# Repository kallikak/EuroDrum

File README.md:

# EuroDrum
Firmware source and schematics for the "Hit It!" Eurorack module.

<table>
  <tr>
    <td></td>
    <td></td>
    <td></td>
  </tr>  
</table>

This YouTube video gives a [brief overview](https://youtu.be/IKqNawbhtcc), and this one shows the [pitch CV mode](https://youtu.be/h47teE46W28).

The two encoders on the left let you move a cursor around the LED matrix, and the SET button toggles a connection between a beat (along the top) and a drum sample (down the side).

In "Bar" mode, the bar length is up to 8 beats, and the lit LEDs connect a beat to the instruments to be played on that beat.
In "Poly" mode, the lit LEDs mean play the corresponding instrument once every *n* beats.

Tone controls a LP filter, increasing cutoff until 12 o'clock, then decreasing while adding resonance. Decay is a simple decay envelope, and drive adds waveshaper distortion. Each control has an associated CV input below.

For timing, there is external gate in, as well as an internally generated clock (that is normalled to the gate in), and of course the audio out.

Hitting adjust switches between control modes:

- Normal mode as shown in the images where the encoders and SET button make and break connections.
  - A long press of SET toggles between active and inactive states.
  - A very long press of SET enters barlength mode, where continuing to hold SET while turning the left-right encoder will adjust the bar length for BAR mode.
  - A long press of ADJUST will clear all connections.
  - Continuing to hold ADJUST will restore a default set of connections.
- Levels mode for setting the level of each instrument. A long press of ADJUST will restore the default levels.
- Kit mode for selecting between 7 kits.
  - Each instrument has an alternate sample
  - The pairs are Bass/Clap, Snare/Rimshot, Open-hat/Maracas, Closed-hat/Claves, Crash cymbal/Ride cymbal, Toms/Congas.
  - Access is by selecting one of 7 pre-defined combinations. This way the front markings keep a reasonable meaning when changing the allocation.
  - Cycle kits with the SET button when in this mode (the display will show a letter from A to G).
- Sequencer mode where the outputs are pitch CVs.
  - The CV offset range from -0.41V to +1V corresponding to 8 offsets from down a 4th to up an octave, following a pentatonic major or minor scale. 
  - The SET button switches between scales (a + on the display indicates major and - indicates minor).
  - A long press of adjust will enable and disable the sequencer mode.

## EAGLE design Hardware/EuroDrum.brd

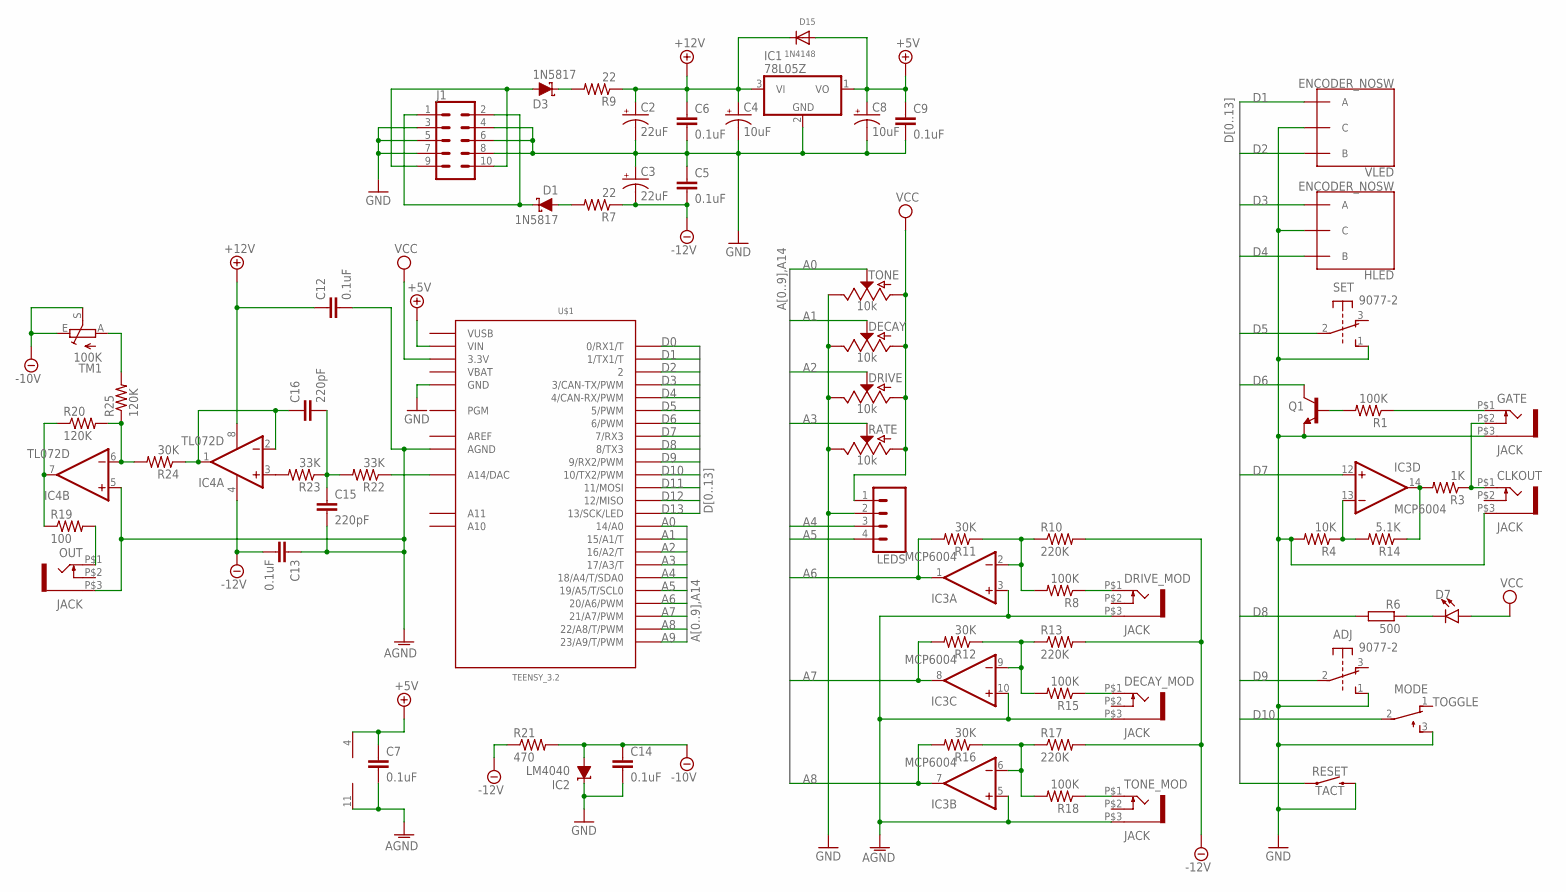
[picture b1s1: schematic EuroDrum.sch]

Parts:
ADJ: 9077-2
C2, C3: 22uF; CPOL-RADIAL-2.5MM-5MM
C4, C8: 10uF; CPOL-RADIAL-2.5MM-5MM
C5, C6, C7, C9, C12, C13, C14: 0.1uF; C0603K
C15, C16: 220pF; C0603K
CLKOUT: JACK; WQP-PJ301M-12_JACK
D1, D3: 1N5817; SOD-323
D7: LED3MM; LED_3MM
D15: 1N4148; SOD-123
DECAY: 10k; POT-PTH-ALPS
DECAY_MOD: JACK; WQP-PJ301M-12_JACK
DRIVE: 10k; POT-PTH-ALPS
DRIVE_MOD: JACK; WQP-PJ301M-12_JACK
GATE: JACK; WQP-PJ301M-12_JACK
HLED: ENCODER_NOSW
IC1: 78L05Z; TO92
IC2: LM4040; DBZ_R-PDSO-G3
IC3: MCP6004; SO14
IC4: TL072D; SO08
J1: CONN_05X2SHD; 2X5-SHROUDED
LEDS: CONN_04LONGPADS; 1X04_LONGPADS
MODE: TOGGLE; TL3XYO
OUT: JACK; WQP-PJ301M-12_JACK
Q1: BC549C; TO92-EBC
R1, R8, R15, R18: 100K; R0603
R3: 1K; R0603
R4: 10K; R0603
R6: 500; R0603
R7, R9: 22; R0603
R10, R13, R17: 220K; R0603
R11, R12, R16, R24: 30K; R0603
R14: 5.1K; R0603
R19: 100; R0603
R20, R25: 120K; R0603
R21: 470; R0603
R22, R23: 33K; R0603
RATE: 10k; POT-PTH-ALPS
RESET: TACT; TACTILE_SWITCH_PTH_6.0MM
SET: 9077-2
TM1: 100K; CA6H
TONE: 10k; POT-PTH-ALPS
TONE_MOD: JACK; WQP-PJ301M-12_JACK
U$1: TEENSY_3.2; TEENSY_3.0-3.2&LC_ALL_PINS
VLED: ENCODER_NOSW

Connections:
+5V: C7.1, C8.1 (+), C9.1, D15.A, IC1.1 (VO), IC3.4 (V+), U$1.VIN
+12V: C2.1 (+), C4.1 (+), C6.1, C12.1, D15.C, IC1.3 (VI), IC4.8 (V+), R9.1
-10V: C14.1, IC2.2 (A), R21.2, TM1.E, TM1.S
-12V: C3.2 (-), C5.2, C13.2, IC4.4 (V-), R7.1, R10.2, R13.2, R17.2, R21.1
A0: TONE.P$2 (S), U$1.14/A0
A1: DECAY.P$2 (S), U$1.15/A1 (15/A1/T)
A2: DRIVE.P$2 (S), U$1.16/A2 (16/A2/T)
A3: RATE.P$2 (S), U$1.17/A3 (17/A3/T)
A4: LEDS.3, U$1.18/A4 (18/A4/T/SDA0)
A5: LEDS.4, U$1.19/A5 (19/A5/T/SCL0)
A6: IC3.1 (OUT), R11.2, U$1.20/A6 (20/A6/PWM)
A7: IC3.8 (OUT), R12.2, U$1.21/A7 (21/A7/PWM)
A8: IC3.7 (OUT), R16.2, U$1.22/A8 (22/A8/T/PWM)
A9: U$1.23/A9 (23/A9/T/PWM)
AGND: C7.2, C12.2, C13.1, C15.2, DECAY_MOD.P$3 (1), DRIVE_MOD.P$3 (1), IC3.3 (+IN), IC3.5 (+IN), IC3.10 (+IN), IC3.11 (V-), IC4.5 (+IN), OUT.P$3 (1), TONE_MOD.P$3 (1), U$1.AGND
AREF: U$1.AREF
D0: U$1.0 (0/RX1/T)
D1: U$1.1 (1/TX1/T), VLED.A
D2: U$1.2, VLED.B
D3: HLED.A, U$1.3 (3/CAN-TX/PWM)
D4: HLED.B, U$1.4 (4/CAN-RX/PWM)
D5: SET.2, U$1.5 (5/PWM)
D6: Q1.C, U$1.6 (6/PWM)
D7: IC3.12 (+IN), U$1.7 (7/RX3)
D8: R6.2, U$1.8 (8/TX3)
D9: ADJ.2, U$1.9 (9/RX2/PWM)
D10: MODE.2, U$1.10 (10/TX2/PWM)
D11: RESET.1, U$1.11 (11/MOSI)
D12: U$1.12 (12/MISO)
D13: U$1.13 (13/SCK/LED)
GND: ADJ.1 (S), C2.2 (-), C3.1 (+), C4.2 (-), C5.1, C6.2, C8.2 (-), C9.2, C14.2, CLKOUT.P$3 (1), DECAY.P$1 (E), DRIVE.P$1 (E), GATE.P$3 (1), HLED.C, IC1.2 (GND), IC2.1 (C), J1.3, J1.4, J1.5, J1.6, J1.7, J1.8, LEDS.2, MODE.3 (S), Q1.E, R4.2, RATE.P$1 (E), RESET.3 (2), SET.1 (S), TONE.P$1 (E), U$1.GND, U$1.GND1 (GND), VLED.C
unnamed: D1.C, J1.1, J1.2
unnamed: IC3.9 (-IN), R12.1, R13.1, R15.2
unnamed: D3.A, J1.9, J1.10
unnamed: D3.C, R9.2
unnamed: DRIVE_MOD.P$1 (2), R8.1
unnamed: D1.A, R7.2
unnamed: IC3.2 (-IN), R8.2, R10.1, R11.1
unnamed: CLKOUT.P$1 (2), GATE.P$2 (3), R3.1
unnamed: DECAY_MOD.P$1 (2), R15.1
unnamed: IC3.6 (-IN), R16.1, R17.1, R18.2
unnamed: R18.1, TONE_MOD.P$1 (2)
unnamed: IC4.3 (+IN), R23.2
unnamed: Q1.B, R1.2
unnamed: C15.1, C16.2, R22.2, R23.1
unnamed: R22.1, U$1.RESET/DAC (A14/DAC)
unnamed: C16.1, IC4.1 (OUT), IC4.2 (-IN), R24.1
unnamed: GATE.P$1 (2), R1.1
unnamed: IC3.13 (-IN), R4.1, R14.2
unnamed: D7.K (C), R6.1
unnamed: IC4.6 (-IN), R20.2, R24.2, R25.1
unnamed: OUT.P$1 (2), R19.2
unnamed: IC4.7 (OUT), R19.1, R20.1
unnamed: R25.2, TM1.A
NOTE1: IC3.14 (OUT), R3.2, R14.1
VBAT: U$1.VBAT
VCC: D7.A, DECAY.P$3 (A), DRIVE.P$3 (A), LEDS.1, RATE.P$3 (A), TONE.P$3 (A), U$1.3.3V, U$1.3.3V1 (3.3V)
VUSB: U$1.VUSB

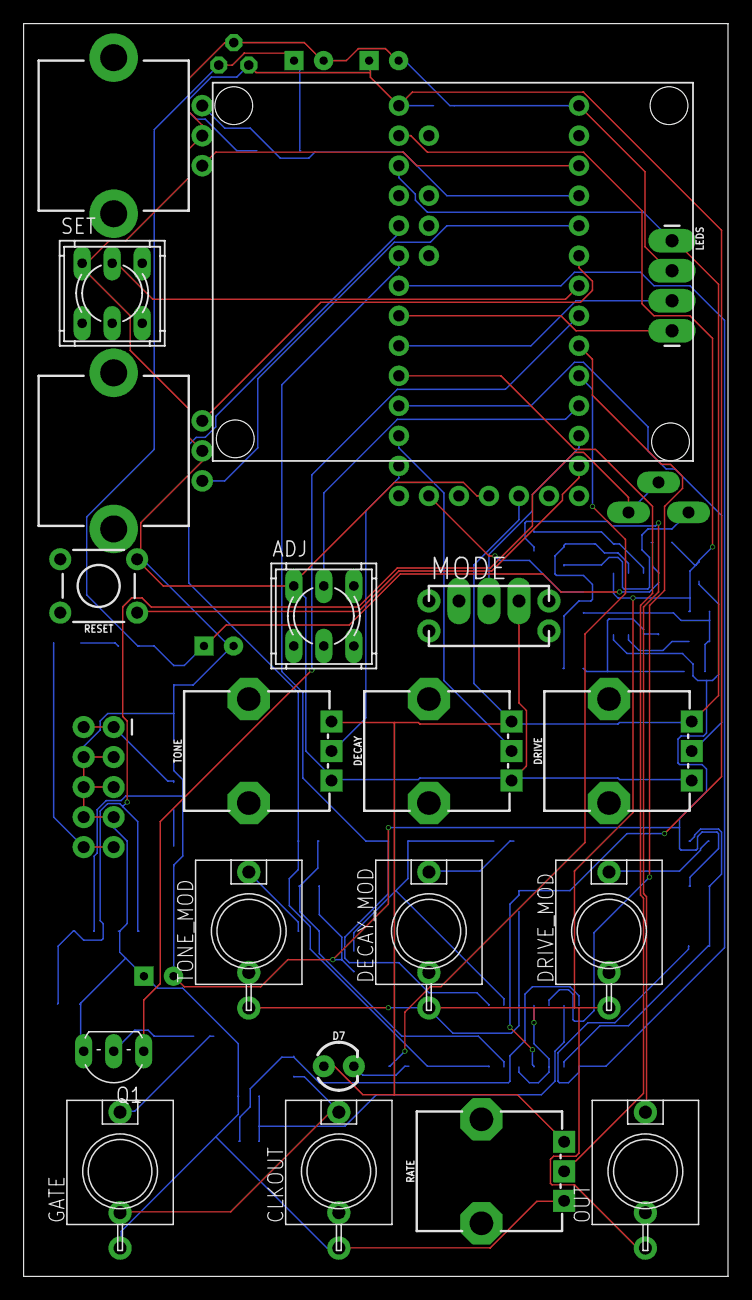
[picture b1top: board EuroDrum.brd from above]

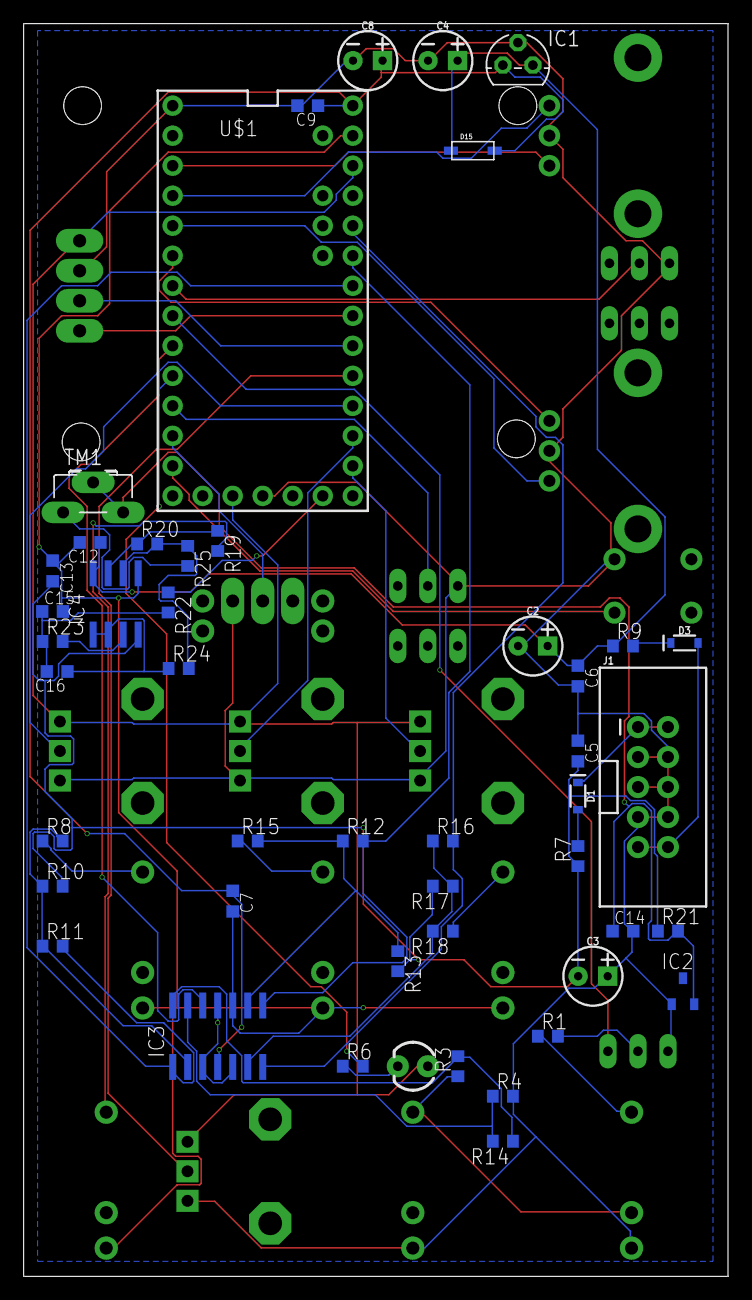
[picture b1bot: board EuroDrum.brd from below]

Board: 2 copper layers, 59.6 x 106.0 mm, 65 parts (46 on the bottom side), 51 nets.

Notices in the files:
parts and their libraries:
SparkFun-Switches: Licensing: Creative Commons ShareAlike 4.0 International - https://creativecommons.org/licenses/by-sa/4.0
